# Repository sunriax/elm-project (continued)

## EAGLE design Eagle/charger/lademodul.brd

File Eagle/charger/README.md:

# elmProject EAGLE files
## Lademodul

### Files
1. Library:
		lademodul.lbr

1. Schematic:
		lademodul.sch
		lademodul.pdf

1. Board:
		mainboard.brd
		layout.pdf

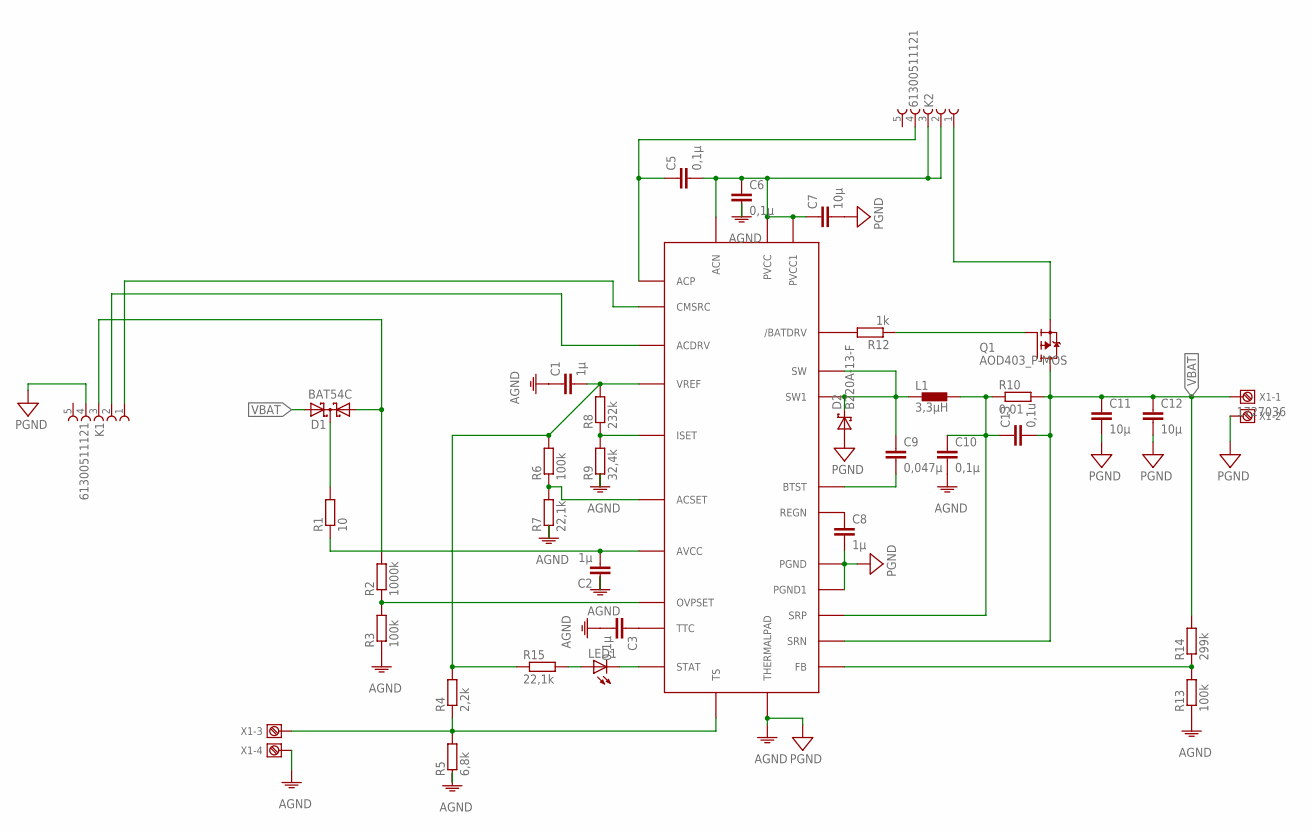
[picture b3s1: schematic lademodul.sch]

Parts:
C1, C2, C8: 1µ; C0603
C3, C5, C6, C10: 0,1µ; C0603
C7, C11, C12: 10µ; C0603
C9: 0,047µ; C0603
C13: 0,1u; C0603
D1: BAT54C; SOT23
D2: B220A-13-F; SMA
IC1: BQ24171; R-PVQFN-N24
K1, K2: 61300511121
L1: 3,3µH; L
LED1: LEDCHIP-LED0603; CHIP-LED0603
Q1: AOD403_P-MOS; TO252
R1: 10; R1206
R2: 1000k; R0603
R3, R6, R13: 100k; R0603
R4: 2,2k; R0603
R5: 6,8k; R0603
R7, R15: 22,1k; R0603
R8: 232k; R0603
R9: 32,4k; R0603
R10: 0,01; R1206
R12: 1k; R0603
R14: 299k; R0603
X1: 1727036

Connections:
AGND: C1.1, C2.1, C3.2, C6.2, C10.2, IC1.THERMALPAD, R3.1, R5.1, R7.1, R9.1, R13.1, X1.4
unnamed: IC1.18 (OVPSET), R2.1, R3.2
unnamed: IC1.10 (TS), R4.1, R5.2, X1.3
unnamed: D1.1 (A1), K1.3, R2.2
unnamed: IC1.13 (ISET), R8.1, R9.2
unnamed: C1.2, IC1.12 (VREF), R4.2, R6.2, R8.2, R15.1
unnamed: C3.1, IC1.11 (TTC)
unnamed: C8.1, IC1.20 (REGN)
unnamed: IC1.17 (ACSET), R6.1, R7.2
unnamed: IC1.7 (CMSRC), K1.1
unnamed: IC1.8 (ACDRV), K1.2
unnamed: C2.2, IC1.4 (AVCC), R1.1
unnamed: C5.1, IC1.6 (ACP), K2.4
unnamed: IC1.9 (STAT), LED1.C
unnamed: K2.1, Q1.2 (S)
unnamed: IC1.19 (/BATDRV), R12.2
unnamed: Q1.1 (G), R12.1
unnamed: C9.2, IC1.21 (BTST)
unnamed: IC1.14 (FB), R13.2, R14.1
unnamed: D1.3 (CC), R1.2
unnamed: LED1.A, R15.2
PGND: C7.2, C8.2, C11.2, C12.2, D2.A, IC1.22 (PGND), IC1.23 (PGND1), K1.4, X1.2
PVCC: C5.2, C6.1, C7.1, IC1.2 (PVCC), IC1.3 (PVCC1), IC1.5 (ACN), K2.2, K2.3
SRP: C10.1, C13.1, IC1.16 (SRP), L1.P$2 (2), R10.1
SW: C9.1, D2.C (K), IC1.1 (SW), IC1.24 (SW1), L1.P$1 (1)
VBAT: C11.1, C12.1, C13.2, D1.2 (A2), IC1.15 (SRN), Q1.3 (D), R10.2, R14.2, X1.1

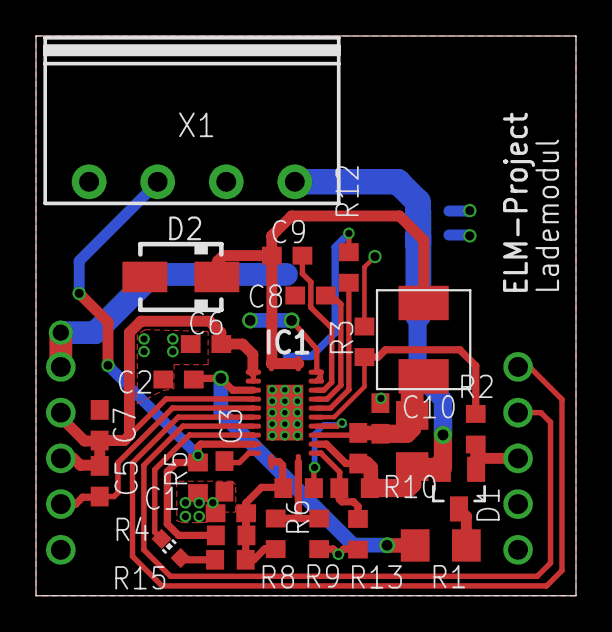
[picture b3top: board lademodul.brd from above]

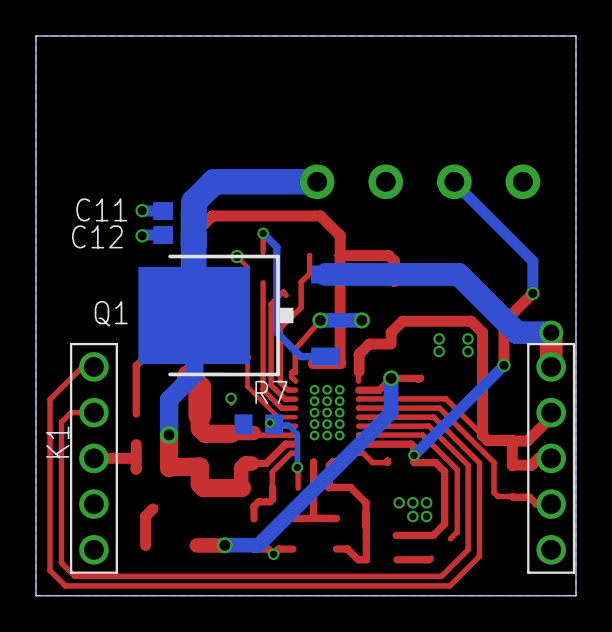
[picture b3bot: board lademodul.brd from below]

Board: 2 copper layers, 30.0 x 31.1 mm, 35 parts (6 on the bottom side), 26 nets.

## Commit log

2017-04-16 :lollipop: Added .gitattributes & .gitignore files
2017-04-16 elmProject INIT
    Start of the elmProject
2017-04-25 Added VGAmodule
    VGA Modul with 1280x1024, 1024x768, 800x600, 640x480 added
2017-05-03 Added Control Unit
